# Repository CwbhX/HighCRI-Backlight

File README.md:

# HighCRI-Backlight
PCB For a high CRI backlight for Film Scanning applications

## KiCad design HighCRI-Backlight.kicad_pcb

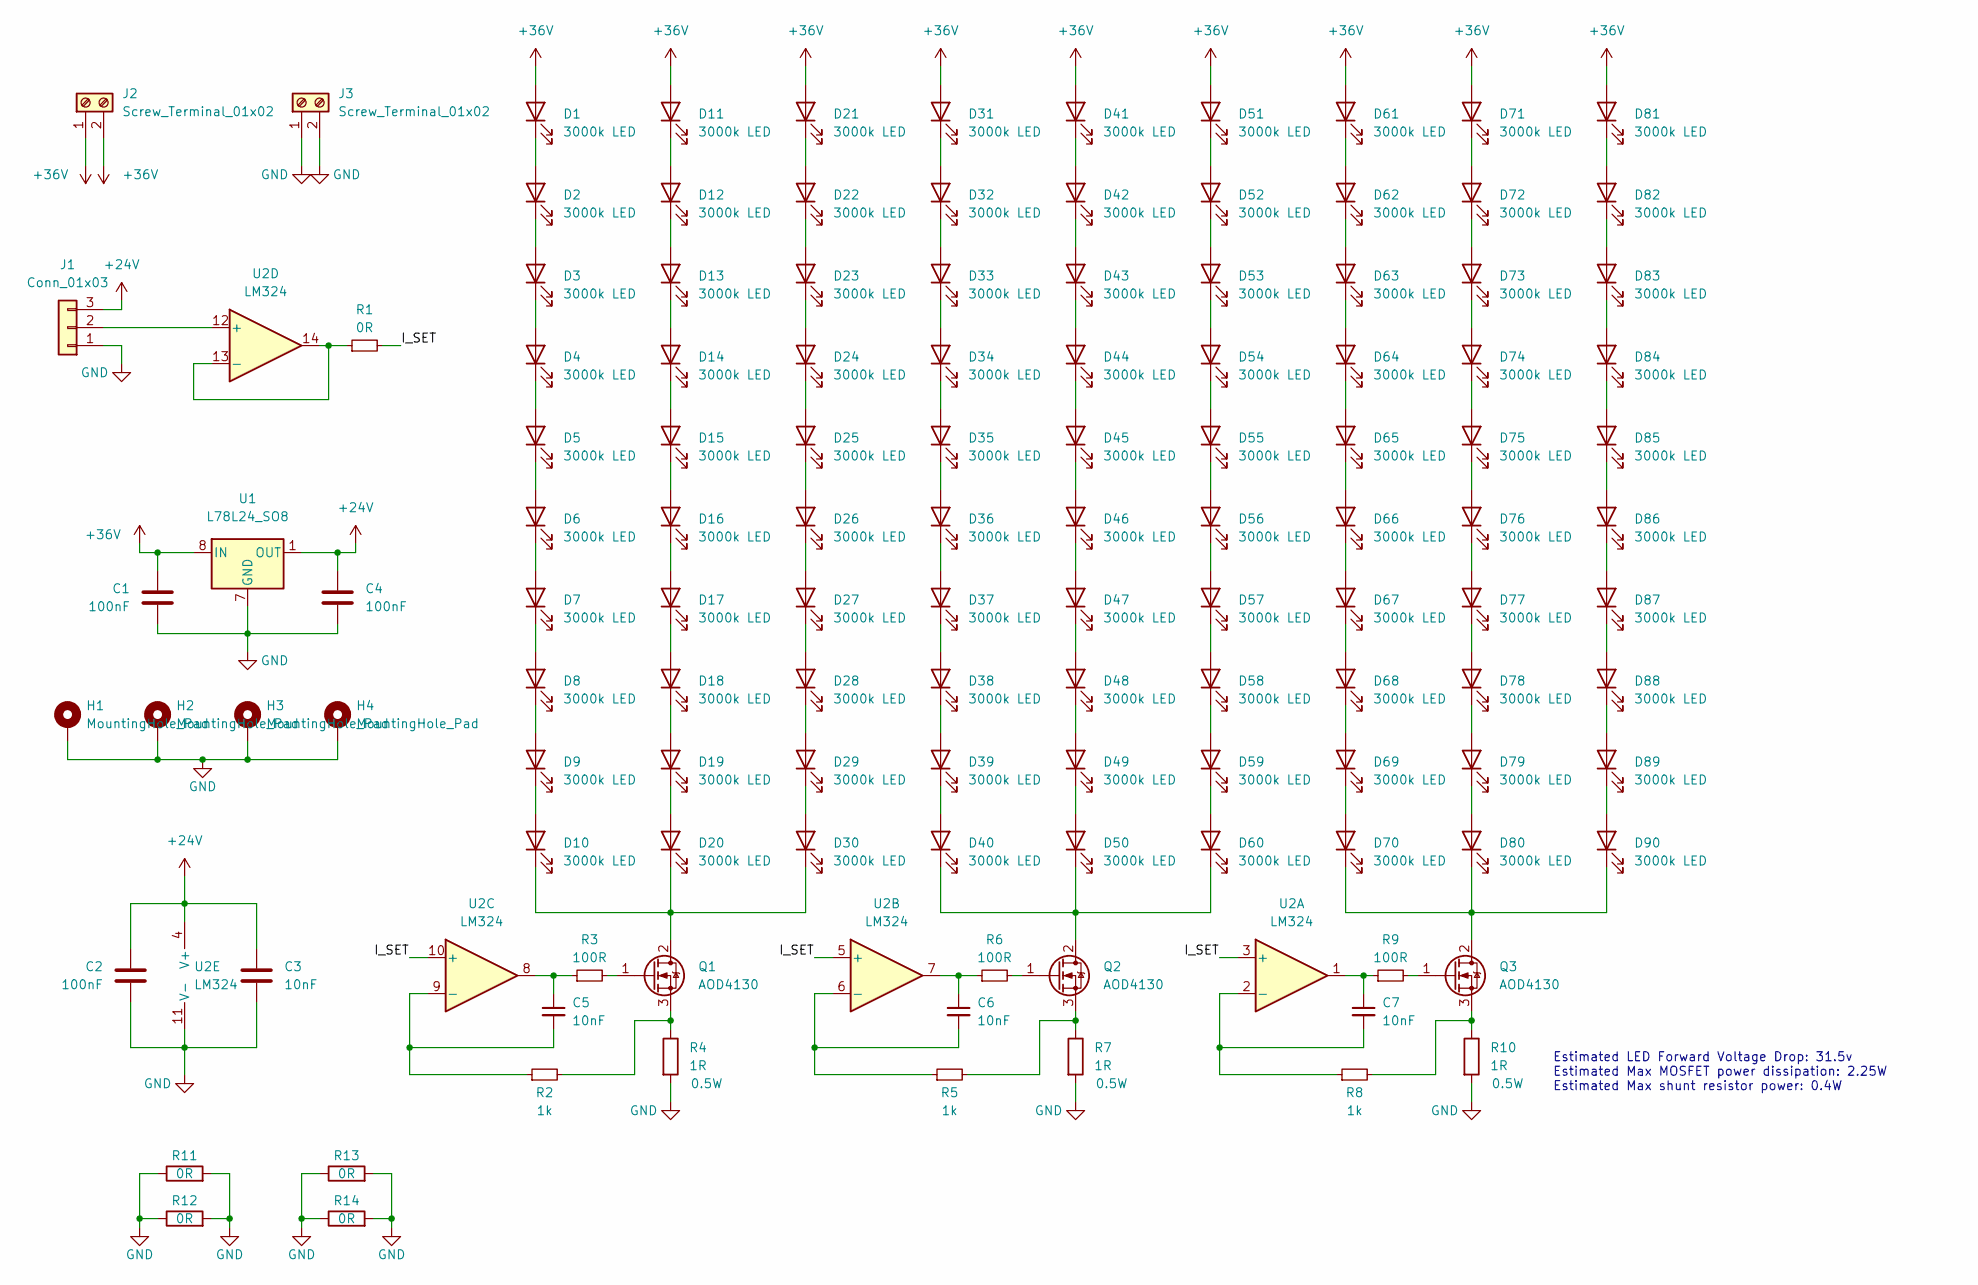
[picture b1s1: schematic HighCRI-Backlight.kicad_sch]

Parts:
C1, C2, C4: 100nF; C_1206_3216Metric_Pad1.33x1.80mm_HandSolder
C3, C5, C6, C7: 10nF; C_1206_3216Metric_Pad1.33x1.80mm_HandSolder
D1, D2, D3, D4, D5, D6, D7, D8, D9, D10, D11, D12, D13, D14, D15, D16, D17, D18, D19, D20, D21, D22, D23, D24, D25, D26, D27, D28, D29, D30, D31, D32, D33, D34, D35, D36, D37, D38, D39, D40, D41, D42, D43, D44, D45, D46, D47, D48, D49, D50, D51, D52, D53, D54, D55, D56, D57, D58, D59, D60, D61, D62, D63, D64, D65, D66, D67, D68, D69, D70, D71, D72, D73, D74, D75, D76, D77, D78, D79, D80, D81, D82, D83, D84, D85, D86, D87, D88, D89, D90: 3000k LED; LED_1212_3030METRIC_MP-3030; MPN MP-3030-1100-30-95; Digikey PN 1214-1339-1-ND
H1, H2, H3, H4: MountingHole_Pad; MountingHole_3.2mm_M3_DIN965_Pad_TopBottom
J1: Conn_01x03; PinHeader_1x03_P2.54mm_Horizontal
J2, J3: Screw_Terminal_01x02; TerminalBlock_bornier-2_P5.08mm
Q1, Q2, Q3: AOD4130; TO-252-2; MPN AOD4130; Digikey PN 785-1216-1-ND
R1, R11, R12, R13, R14: 0R; R_1206_3216Metric_Pad1.30x1.75mm_HandSolder
R2, R5, R8: 1k; R_1206_3216Metric_Pad1.30x1.75mm_HandSolder
R3, R6, R9: 100R; R_1206_3216Metric_Pad1.30x1.75mm_HandSolder
R4, R7, R10: 1R; R_1206_3216Metric_Pad1.30x1.75mm_HandSolder; MPN RMCF1210JT1R00; Digikey PN RMCF1210JT1R00CT-ND
U1: L78L24_SO8; SOIC-8_3.9x4.9mm_P1.27mm
U2: LM324; SOIC-14_3.9x8.7mm_P1.27mm

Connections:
+24V: C2.2, C3.1, C4.1, J1.3, U1.1 (OUT), U2.4 (V+)
+36V: C1.2, D1.2 (A), D11.2 (A), D21.2 (A), D31.2 (A), D41.2 (A), D51.2 (A), D61.2 (A), D71.2 (A), D81.2 (A), J2.1, J2.2, U1.8 (IN)
/I_SET: R1.2, U2.3 (+), U2.5 (+), U2.10 (+)
GND: C1.1, C2.1, C3.2, C4.2, H1.1, H2.1, H3.1, H4.1, J1.1, J3.1, J3.2, R4.2, R7.2, R10.2, R11.1, R11.2, R12.1, R12.2, R13.1, R13.2, R14.1, R14.2, U1.2 (GND), U1.3 (GND), U1.6 (GND), U1.7 (GND), U2.11 (V-)
unnamed: C5.1, R3.1, U2.8
unnamed: C5.2, R2.1, U2.9 (-)
unnamed: C6.1, R6.1, U2.7
unnamed: C6.2, R5.1, U2.6 (-)
unnamed: C7.1, R9.1, U2.1
unnamed: C7.2, R8.1, U2.2 (-)
unnamed: D1.1 (K), D2.2 (A)
unnamed: D2.1 (K), D3.2 (A)
unnamed: D3.1 (K), D4.2 (A)
unnamed: D4.1 (K), D5.2 (A)
unnamed: D5.1 (K), D6.2 (A)
unnamed: D6.1 (K), D7.2 (A)
unnamed: D7.1 (K), D8.2 (A)
unnamed: D8.1 (K), D9.2 (A)
unnamed: D10.1 (K), D20.1 (K), D30.1 (K), Q1.2 (D)
unnamed: D9.1 (K), D10.2 (A)
unnamed: D11.1 (K), D12.2 (A)
unnamed: D12.1 (K), D13.2 (A)
unnamed: D13.1 (K), D14.2 (A)
unnamed: D14.1 (K), D15.2 (A)
unnamed: D15.1 (K), D16.2 (A)
unnamed: D16.1 (K), D17.2 (A)
unnamed: D17.1 (K), D18.2 (A)
unnamed: D18.1 (K), D19.2 (A)
unnamed: D19.1 (K), D20.2 (A)
unnamed: D21.1 (K), D22.2 (A)
unnamed: D22.1 (K), D23.2 (A)
unnamed: D23.1 (K), D24.2 (A)
unnamed: D24.1 (K), D25.2 (A)
unnamed: D25.1 (K), D26.2 (A)
unnamed: D26.1 (K), D27.2 (A)
unnamed: D27.1 (K), D28.2 (A)
unnamed: D28.1 (K), D29.2 (A)
unnamed: D29.1 (K), D30.2 (A)
unnamed: D31.1 (K), D32.2 (A)
unnamed: D32.1 (K), D33.2 (A)
unnamed: D33.1 (K), D34.2 (A)
unnamed: D34.1 (K), D35.2 (A)
unnamed: D35.1 (K), D36.2 (A)
unnamed: D36.1 (K), D37.2 (A)
unnamed: D37.1 (K), D38.2 (A)
unnamed: D38.1 (K), D39.2 (A)
unnamed: D39.1 (K), D40.2 (A)
unnamed: D40.1 (K), D50.1 (K), D60.1 (K), Q2.2 (D)
unnamed: D41.1 (K), D42.2 (A)
unnamed: D42.1 (K), D43.2 (A)
unnamed: D43.1 (K), D44.2 (A)
unnamed: D44.1 (K), D45.2 (A)
unnamed: D45.1 (K), D46.2 (A)
unnamed: D46.1 (K), D47.2 (A)
unnamed: D47.1 (K), D48.2 (A)
unnamed: D48.1 (K), D49.2 (A)
unnamed: D49.1 (K), D50.2 (A)
unnamed: D51.1 (K), D52.2 (A)
unnamed: D52.1 (K), D53.2 (A)
unnamed: D53.1 (K), D54.2 (A)
unnamed: D54.1 (K), D55.2 (A)
unnamed: D55.1 (K), D56.2 (A)
unnamed: D56.1 (K), D57.2 (A)
unnamed: D57.1 (K), D58.2 (A)
unnamed: D58.1 (K), D59.2 (A)
unnamed: D59.1 (K), D60.2 (A)
unnamed: D61.1 (K), D62.2 (A)
unnamed: D62.1 (K), D63.2 (A)
unnamed: D63.1 (K), D64.2 (A)
unnamed: D64.1 (K), D65.2 (A)
unnamed: D65.1 (K), D66.2 (A)
unnamed: D66.1 (K), D67.2 (A)
unnamed: D67.1 (K), D68.2 (A)
unnamed: D68.1 (K), D69.2 (A)
unnamed: D69.1 (K), D70.2 (A)
unnamed: D70.1 (K), D80.1 (K), D90.1 (K), Q3.2 (D)
unnamed: D71.1 (K), D72.2 (A)
unnamed: D72.1 (K), D73.2 (A)
unnamed: D73.1 (K), D74.2 (A)
unnamed: D74.1 (K), D75.2 (A)
unnamed: D75.1 (K), D76.2 (A)
unnamed: D76.1 (K), D77.2 (A)
unnamed: D77.1 (K), D78.2 (A)
unnamed: D78.1 (K), D79.2 (A)
unnamed: D79.1 (K), D80.2 (A)
unnamed: D81.1 (K), D82.2 (A)
unnamed: D82.1 (K), D83.2 (A)
unnamed: D83.1 (K), D84.2 (A)
unnamed: D84.1 (K), D85.2 (A)
unnamed: D85.1 (K), D86.2 (A)
unnamed: D86.1 (K), D87.2 (A)
unnamed: D87.1 (K), D88.2 (A)
unnamed: D88.1 (K), D89.2 (A)
unnamed: D89.1 (K), D90.2 (A)
unnamed: J1.2, U2.12 (+)
unnamed: Q1.1 (G), R3.2
unnamed: Q1.3 (S), R2.2, R4.1
unnamed: Q2.1 (G), R6.2
unnamed: Q2.3 (S), R5.2, R7.1
unnamed: Q3.1 (G), R9.2
unnamed: Q3.3 (S), R8.2, R10.1
unnamed: R1.1, U2.13 (-), U2.14

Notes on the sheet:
Estimated LED Forward Voltage Drop: 31.5v Estimated Max MOSFET power dissipation: 2.25W Estimated Max shunt resistor power: 0.4W

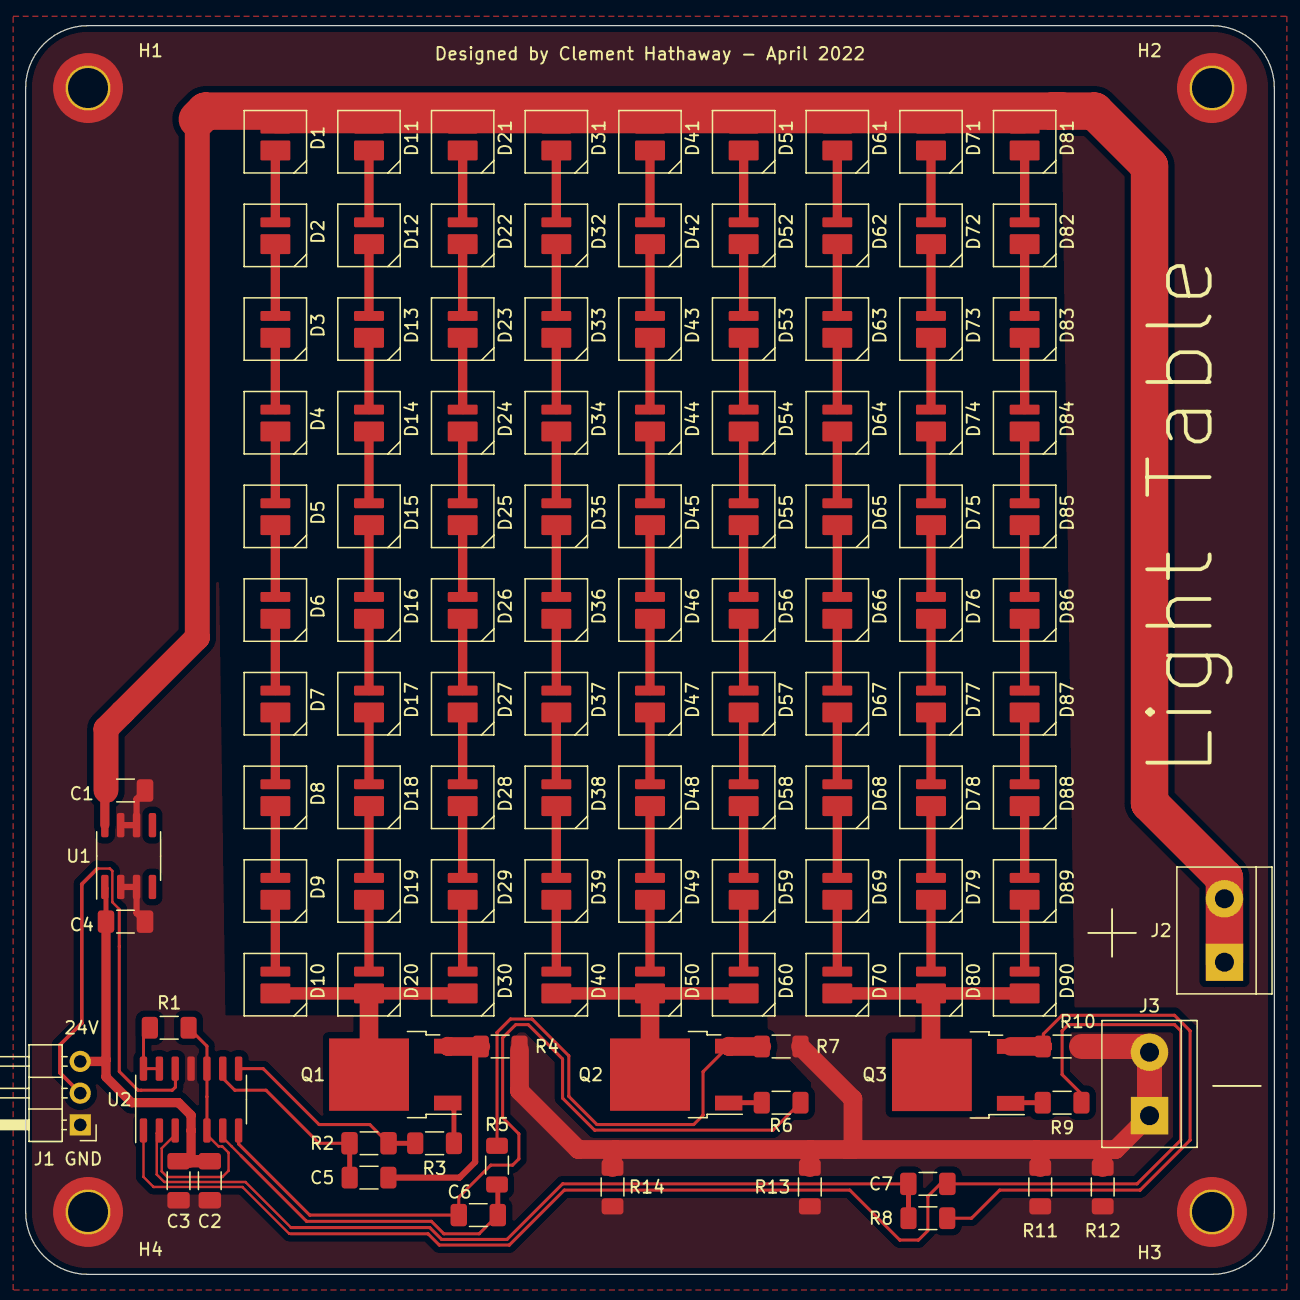
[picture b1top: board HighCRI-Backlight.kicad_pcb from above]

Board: 2 copper layers, 100.0 x 100.0 mm, 123 parts (0 on the bottom side), 102 nets.

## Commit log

2022-04-02 Schematic Done
2022-04-02 Basic PCB Layout
2022-04-02 Routing Seemingly Complete
2022-04-02 Silkscreening
2022-04-02 Added lightbulb symbol to back
2022-04-03 Fixed gitignore stuff
2022-04-03 Finished Single Sided Design
2022-04-04 Minor errors
2022-04-04 Fixed some things
    KiCAD still glitching on jumper resistors
2022-04-04 Saved
